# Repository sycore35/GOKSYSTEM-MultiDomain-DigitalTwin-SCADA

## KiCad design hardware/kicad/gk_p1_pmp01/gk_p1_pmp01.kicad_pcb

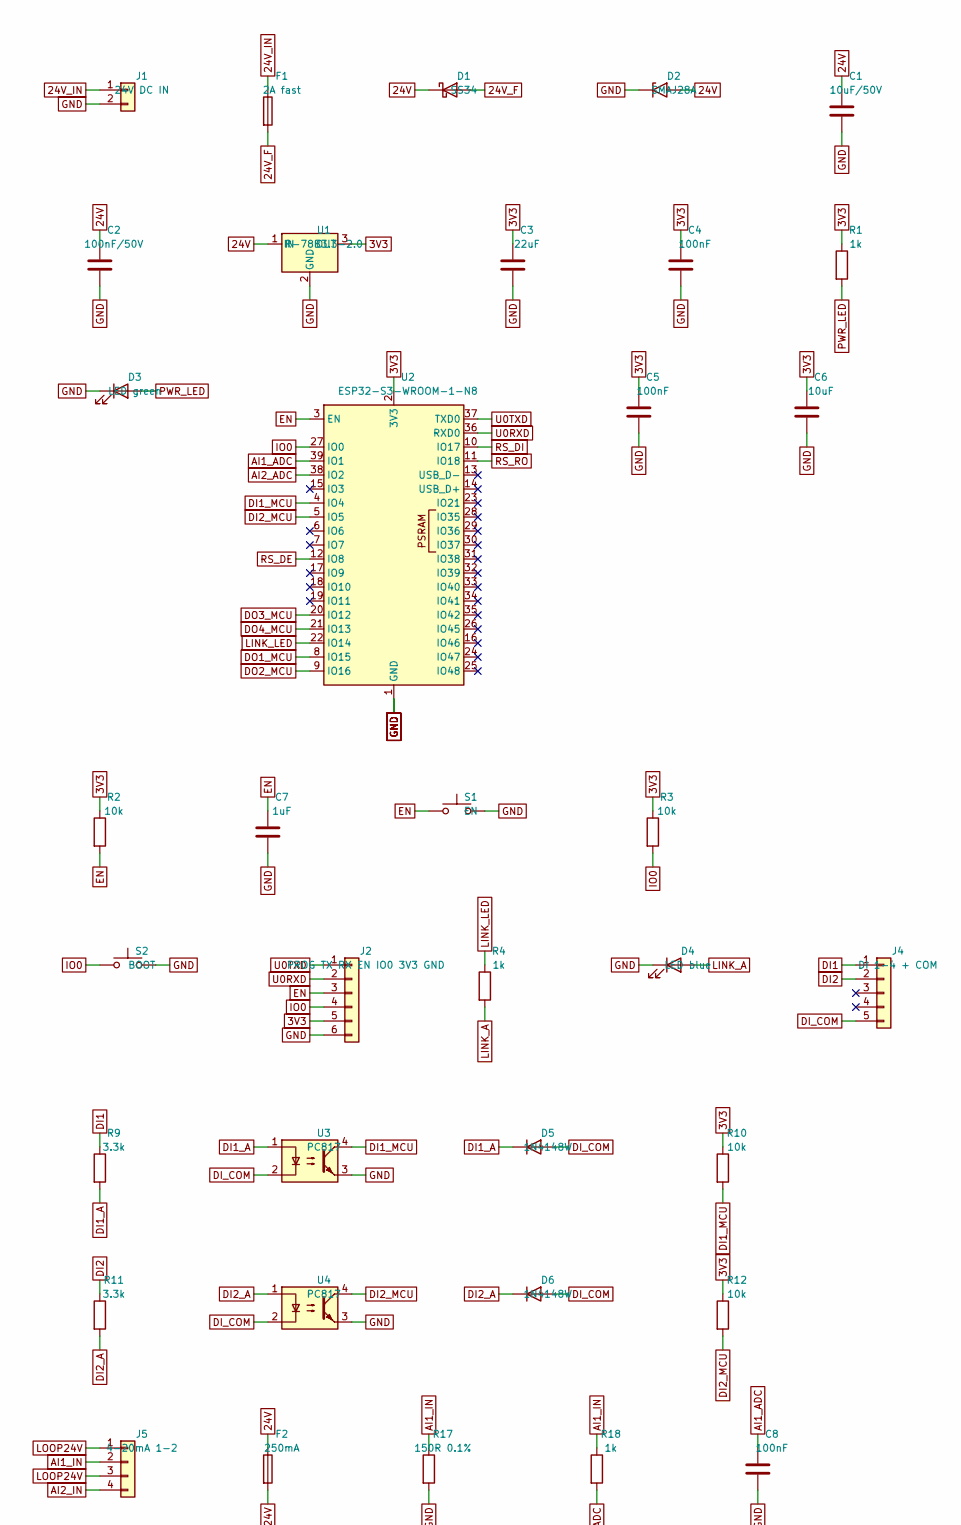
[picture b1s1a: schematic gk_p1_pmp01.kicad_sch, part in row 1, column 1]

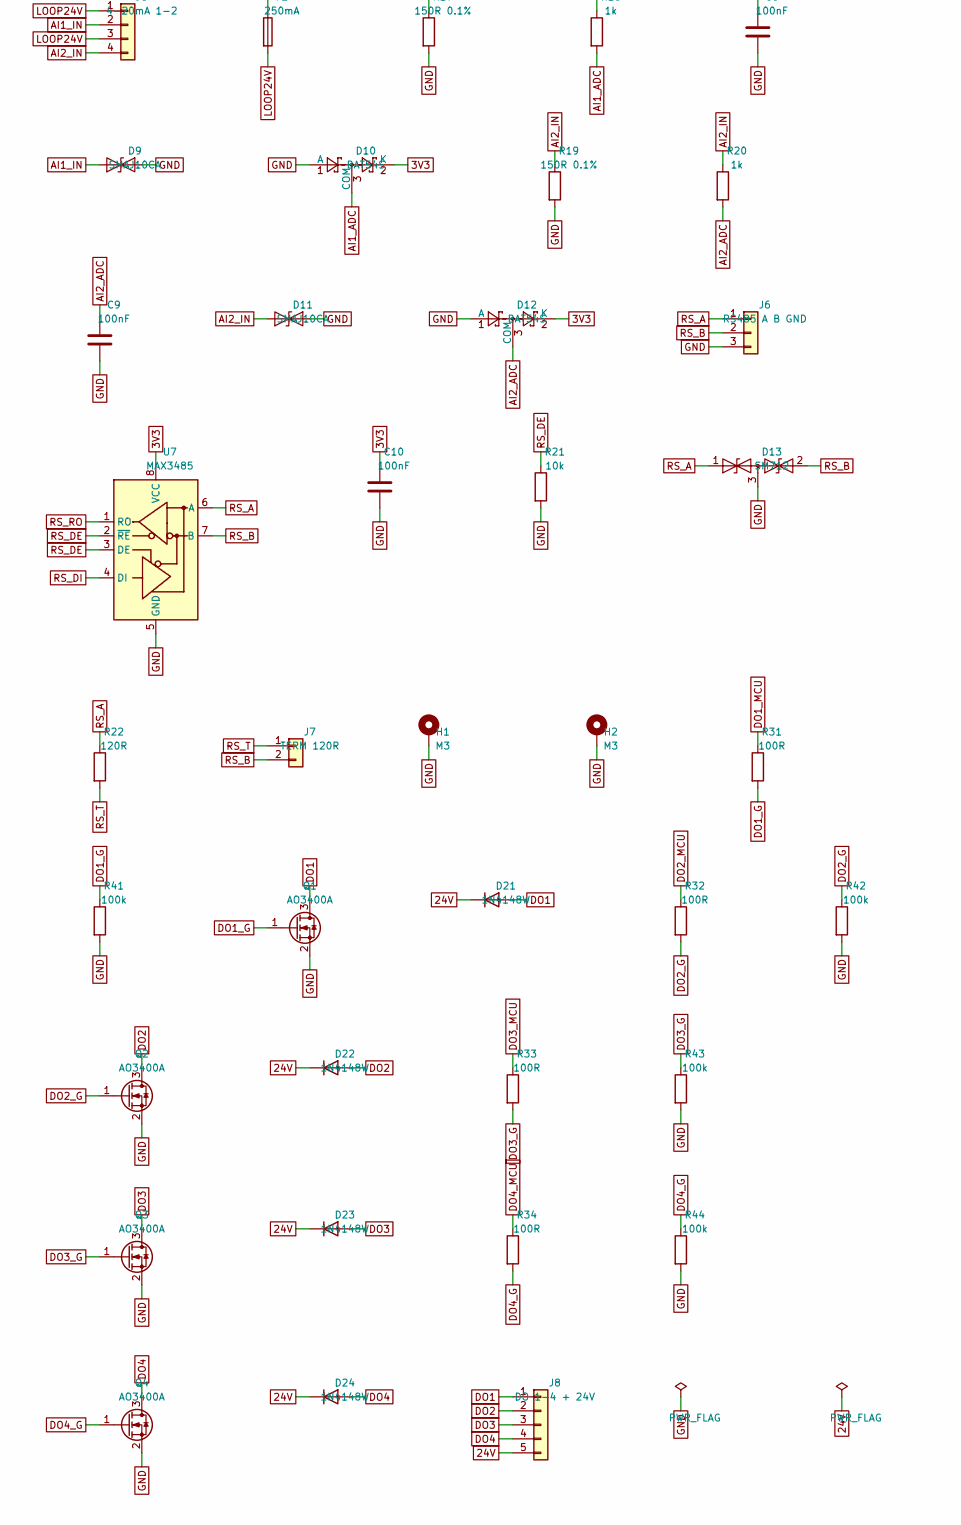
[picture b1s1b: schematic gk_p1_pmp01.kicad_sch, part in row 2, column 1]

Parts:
C1: 10uF/50V; C_1210_3225Metric
C2: 100nF/50V; C_0603_1608Metric
C3: 22uF; C_0805_2012Metric
C4, C5, C8, C9, C10: 100nF; C_0603_1608Metric
C6: 10uF; C_0805_2012Metric
C7: 1uF; C_0603_1608Metric
D1: SS34; D_SMA
D2: SMAJ28A; D_SMA
D3: LED green; LED_0603_1608Metric
D4: LED blue; LED_0603_1608Metric
D5, D6, D21, D22, D23, D24: 1N4148W; D_SOD-123
D9, D11: SMAJ10CA; D_SMA
D10, D12: BAT54S; SOT-23
D13: SM712; SOT-23
F1: 2A fast; Fuse_1206_3216Metric
F2: 250mA; Fuse_1206_3216Metric
H1, H2: M3; MountingHole_3.2mm_M3_Pad
J1: 24V DC IN; PhoenixContact_MSTBA_2,5_2-G-5,08_1x02_P5.08mm_Horizontal
J2: PROG TX RX EN IO0 3V3 GND; PinHeader_1x06_P2.54mm_Vertical
J4: DI 1-4 + COM; PhoenixContact_MC_1,5_5-G-3.5_1x05_P3.50mm_Horizontal
J5: 4-20mA 1-2; PhoenixContact_MC_1,5_4-G-3.5_1x04_P3.50mm_Horizontal
J6: RS485 A B GND; PhoenixContact_MC_1,5_3-G-3.5_1x03_P3.50mm_Horizontal
J7: TERM 120R; PinHeader_1x02_P2.54mm_Vertical
J8: DO 1-4 + 24V; PhoenixContact_MC_1,5_5-G-3.5_1x05_P3.50mm_Horizontal
Q1, Q2, Q3, Q4: AO3400A; SOT-23
R1, R4, R18, R20: 1k; R_0603_1608Metric
R2, R3, R10, R12, R21: 10k; R_0603_1608Metric
R9, R11: 3.3k; R_1206_3216Metric
R17, R19: 150R 0.1%; R_0603_1608Metric
R22: 120R; R_0603_1608Metric
R31, R32, R33, R34: 100R; R_0603_1608Metric
R41, R42, R43, R44: 100k; R_0603_1608Metric
S1: EN; SW_SPST_TL3342
S2: BOOT; SW_SPST_TL3342
U1: R-78B3.3-2.0; Converter_DCDC_RECOM_R-78B-2.0_THT
U2: ESP32-S3-WROOM-1-N8; ESP32-S3-WROOM-1
U3, U4: PC817; SOP-4_7.5x4.1mm_P2.54mm
U7: MAX3485; SOIC-8_3.9x4.9mm_P1.27mm

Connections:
3V3: C3.1, C4.1, C5.1, C6.1, C10.1, D10.2 (K), D12.2 (K), J2.5, R1.1, R2.1, R3.1, R10.1, R12.1, U1.3 (OUT), U2.2 (3V3), U7.8 (VCC)
24V: C1.1, C2.1, D1.1 (K), D2.2 (A2), D21.1 (K), D22.1 (K), D23.1 (K), D24.1 (K), F2.1, J8.5, U1.1 (IN)
24V_F: D1.2 (A), F1.2
24V_IN: F1.1, J1.1
AI1_ADC: C8.1, D10.3 (COM), R18.2, U2.39 (IO1)
AI1_IN: D9.1 (A1), J5.2, R17.1, R18.1
AI2_ADC: C9.1, D12.3 (COM), R20.2, U2.38 (IO2)
AI2_IN: D11.1 (A1), J5.4, R19.1, R20.1
DI1: J4.1, R9.1
DI1_A: D5.1 (K), R9.2, U3.1
DI1_MCU: R10.2, U2.4 (IO4), U3.4
DI2: J4.2, R11.1
DI2_A: D6.1 (K), R11.2, U4.1
DI2_MCU: R12.2, U2.5 (IO5), U4.4
DI_COM: D5.2 (A), D6.2 (A), J4.5, U3.2, U4.2
DO1: D21.2 (A), J8.1, Q1.3 (D)
DO1_G: Q1.1 (G), R31.2, R41.1
DO1_MCU: R31.1, U2.8 (IO15)
DO2: D22.2 (A), J8.2, Q2.3 (D)
DO2_G: Q2.1 (G), R32.2, R42.1
DO2_MCU: R32.1, U2.9 (IO16)
DO3: D23.2 (A), J8.3, Q3.3 (D)
DO3_G: Q3.1 (G), R33.2, R43.1
DO3_MCU: R33.1, U2.20 (IO12)
DO4: D24.2 (A), J8.4, Q4.3 (D)
DO4_G: Q4.1 (G), R34.2, R44.1
DO4_MCU: R34.1, U2.21 (IO13)
EN: C7.1, J2.3, R2.2, S1.1, U2.3 (EN)
GND: C1.2, C2.2, C3.2, C4.2, C5.2, C6.2, C7.2, C8.2, C9.2, C10.2, D2.1 (A1), D3.1 (K), D4.1 (K), D9.2 (A2), D10.1 (A), D11.2 (A2), D12.1 (A), D13.3 (common), H1.1, H2.1, J1.2, J2.6, J6.3, Q1.2 (S), Q2.2 (S), Q3.2 (S), Q4.2 (S), R17.2, R19.2, R21.2, R41.2, R42.2, R43.2, R44.2, S1.2, S2.2, U1.2 (GND), U2.1 (GND), U2.40 (GND), U2.41 (GND), U3.3, U4.3, U7.5 (GND)
IO0: J2.4, R3.2, S2.1, U2.27 (IO0)
LINK_A: D4.2 (A), R4.2
LINK_LED: R4.1, U2.22 (IO14)
LOOP24V: F2.2, J5.1, J5.3
PWR_LED: D3.2 (A), R1.2
RS_A: D13.1 (A1), J6.1, R22.1, U7.6 (A)
RS_B: D13.2 (A2), J6.2, J7.2, U7.7 (B)
RS_DE: R21.1, U2.12 (IO8), U7.2 (~RE), U7.3 (DE)
RS_DI: U2.10 (IO17), U7.4 (DI)
RS_RO: U2.11 (IO18), U7.1 (RO)
RS_T: J7.1, R22.2
U0RXD: J2.2, U2.36 (RXD0)
U0TXD: J2.1, U2.37 (TXD0)

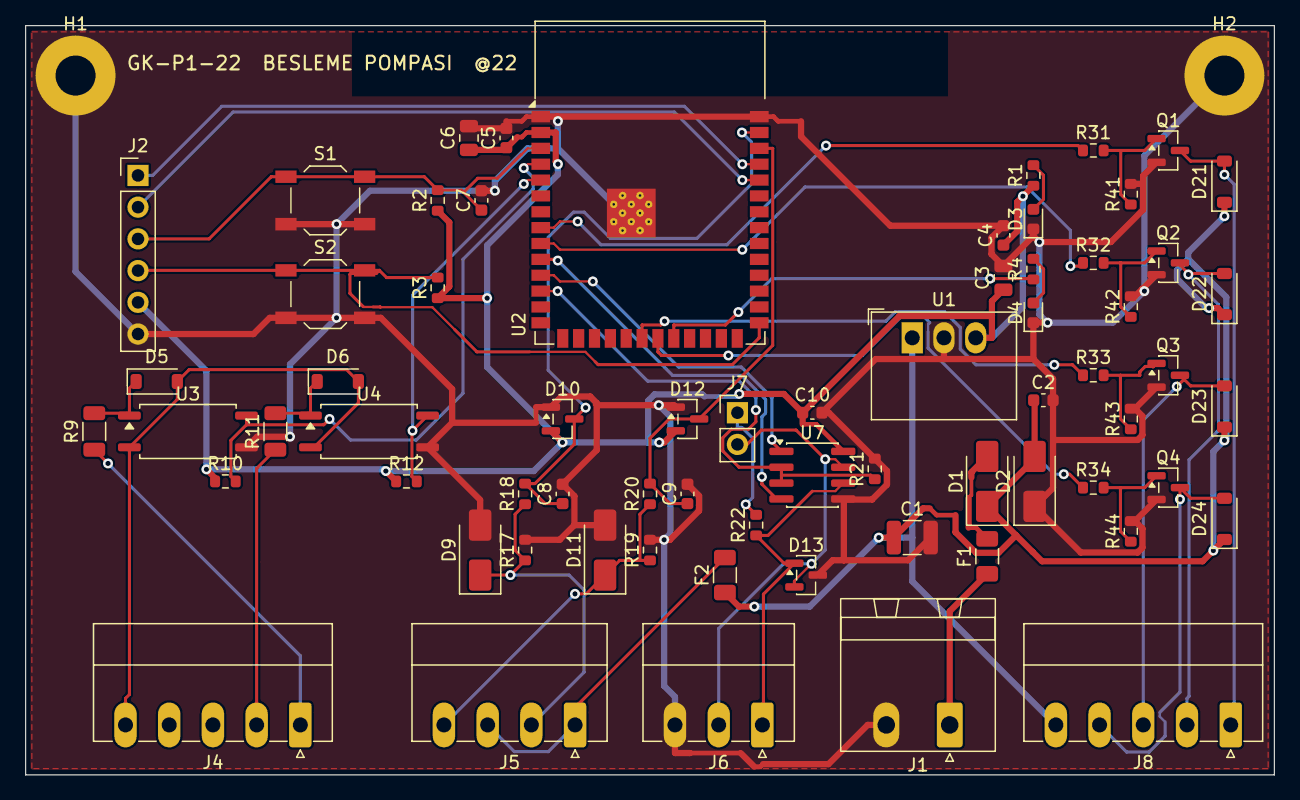
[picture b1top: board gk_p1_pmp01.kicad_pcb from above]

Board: 2 copper layers, 100.0 x 60.0 mm, 69 parts (0 on the bottom side), 42 nets.

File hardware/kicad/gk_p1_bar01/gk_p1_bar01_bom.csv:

"Designator","Value","Footprint","MPN","Manufacturer","Qty"
"C1","10uF/50V","Capacitor_SMD:C_1210_3225Metric","","","1"
"C2","100nF/50V","Capacitor_SMD:C_0603_1608Metric","","","1"
"C3","22uF","Capacitor_SMD:C_0805_2012Metric","","","1"
"C4,C5,C8,C10","100nF","Capacitor_SMD:C_0603_1608Metric","","","4"
"C6","10uF","Capacitor_SMD:C_0805_2012Metric","","","1"
"C7","1uF","Capacitor_SMD:C_0603_1608Metric","","","1"
"D1","SS34","Diode_SMD:D_SMA","","","1"
"D2","SMAJ28A","Diode_SMD:D_SMA","","","1"
"D3","LED green","LED_SMD:LED_0603_1608Metric","","","1"
"D4","LED blue","LED_SMD:LED_0603_1608Metric","","","1"
"D5,D6,D21,D22","1N4148W","Diode_SMD:D_SOD-123","","","4"
"D9","SMAJ10CA","Diode_SMD:D_SMA","","","1"
"D10","BAT54S","Package_TO_SOT_SMD:SOT-23","","","1"
"D13","SM712","Package_TO_SOT_SMD:SOT-23","","","1"
"F1","2A fast","Fuse:Fuse_1206_3216Metric","","","1"
"F2","250mA","Fuse:Fuse_1206_3216Metric","","","1"
"H1,H2","M3","MountingHole:MountingHole_3.2mm_M3_Pad","","","2"
"J1","24V DC IN","Connector_Phoenix_MSTB:PhoenixContact_MSTBA_2,5_2-G-5,08_1x02_P5.08mm_Horizontal","","","1"
"J2","PROG TX RX EN IO0 3V3 GND","Connector_PinHeader_2.54mm:PinHeader_1x06_P2.54mm_Vertical","","","1"
"J4","DI 1-4 + COM","Connector_Phoenix_MC:PhoenixContact_MC_1,5_5-G-3.5_1x05_P3.50mm_Horizontal","","","1"
"J5","4-20mA 1-2","Connector_Phoenix_MC:PhoenixContact_MC_1,5_4-G-3.5_1x04_P3.50mm_Horizontal","","","1"
"J6","RS485 A B GND","Connector_Phoenix_MC:PhoenixContact_MC_1,5_3-G-3.5_1x03_P3.50mm_Horizontal","","","1"
"J7","TERM 120R","Connector_PinHeader_2.54mm:PinHeader_1x02_P2.54mm_Vertical","","","1"
"J8","DO 1-4 + 24V","Connector_Phoenix_MC:PhoenixContact_MC_1,5_5-G-3.5_1x05_P3.50mm_Horizontal","","","1"
"Q1,Q2","AO3400A","Package_TO_SOT_SMD:SOT-23","","","2"
"R1,R4,R18","1k","Resistor_SMD:R_0603_1608Metric","","","3"
"R2,R3,R10,R12,R21","10k","Resistor_SMD:R_0603_1608Metric","","","5"
"R9,R11","3.3k","Resistor_SMD:R_1206_3216Metric","","","2"
"R17","150R 0.1%","Resistor_SMD:R_0603_1608Metric","","","1"
"R22","120R","Resistor_SMD:R_0603_1608Metric","","","1"
"R31,R32","100R","Resistor_SMD:R_0603_1608Metric","","","2"
"R41,R42","100k","Resistor_SMD:R_0603_1608Metric","","","2"
"S1","EN","Button_Switch_SMD:SW_SPST_TL3342","","","1"
"S2","BOOT","Button_Switch_SMD:SW_SPST_TL3342","","","1"
"U1","R-78B3.3-2.0","Converter_DCDC:Converter_DCDC_RECOM_R-78B-2.0_THT","","","1"
"U2","ESP32-S3-WROOM-1-N8","RF_Module:ESP32-S3-WROOM-1","","","1"
"U3,U4","PC817","Package_SO:SOP-4_7.5x4.1mm_P2.54mm","","","2"
"U7","MAX3485","Package_SO:SOIC-8_3.9x4.9mm_P1.27mm","","","1"
